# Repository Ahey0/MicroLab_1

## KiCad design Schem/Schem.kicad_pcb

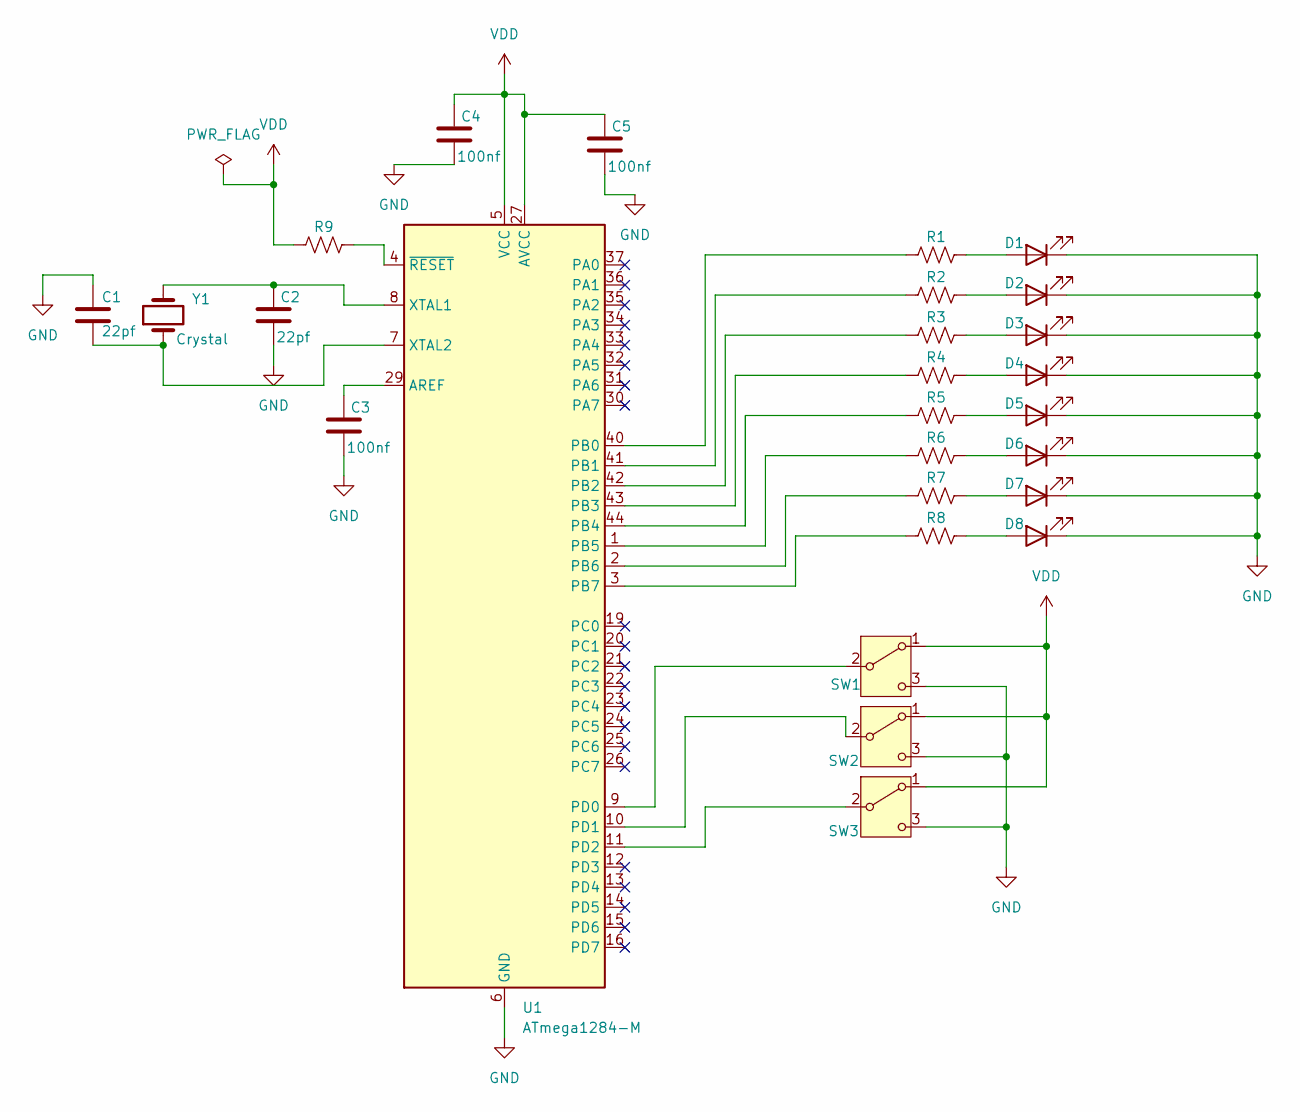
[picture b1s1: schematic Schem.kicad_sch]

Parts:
C1, C2: 22pf; C_0201_0603Metric
C3, C4, C5: 100nf; C_0201_0603Metric
D1, D2, D3, D5, D6, D7, D8: LED; LED_D3.0mm
D4: LED; LED_D3.0mm_FlatTop
R1, R2, R3, R4, R5, R6, R7, R8, R9: 10k; R_0402_1005Metric
SW1, SW2, SW3: SW_SPDT; SW_Slide_SPDT_Straight_CK_OS102011MS2Q
U1: ATmega1284-M; QFN-44-1EP_7x7mm_P0.5mm_EP5.2x5.2mm
Y1: Crystal; Crystal_SMD_EuroQuartz_EQ161-2Pin_3.2x1.5mm

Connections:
GND: C1.1, C2.2, C3.2, C4.2, C5.2, D1.1 (K), D2.1 (K), D3.1 (K), D4.1 (K), D5.1 (K), D6.1 (K), D7.1 (K), D8.1 (K), SW1.3 (C), SW2.3 (C), SW3.3 (C), U1.6 (GND), U1.18 (GND), U1.28 (GND), U1.39 (GND), U1.45 (GND)
unnamed: D1.2 (A), R1.2
unnamed: D2.2 (A), R2.2
unnamed: D3.2 (A), R3.2
unnamed: D4.2 (A), R4.2
unnamed: D5.2 (A), R5.2
unnamed: D6.2 (A), R6.2
unnamed: D7.2 (A), R7.2
unnamed: D8.2 (A), R8.2
unnamed: SW1.2 (B), U1.9 (PD0)
unnamed: SW2.2 (B), U1.10 (PD1)
unnamed: SW3.2 (B), U1.11 (PD2)
unnamed: C3.1, U1.29 (AREF)
unnamed: R1.1, U1.40 (PB0)
unnamed: R2.1, U1.41 (PB1)
unnamed: R3.1, U1.42 (PB2)
unnamed: R4.1, U1.43 (PB3)
unnamed: R5.1, U1.44 (PB4)
unnamed: R6.1, U1.1 (PB5)
unnamed: R7.1, U1.2 (PB6)
unnamed: R8.1, U1.3 (PB7)
unnamed: C2.1, U1.8 (XTAL1), Y1.2
unnamed: C1.2, U1.7 (XTAL2), Y1.1
unnamed: R9.2, U1.4 (~RESET)
VDD: C4.1, C5.1, R9.1, SW1.1 (A), SW2.1 (A), SW3.1 (A), U1.5 (VCC), U1.17 (VCC), U1.27 (AVCC), U1.38 (VCC)

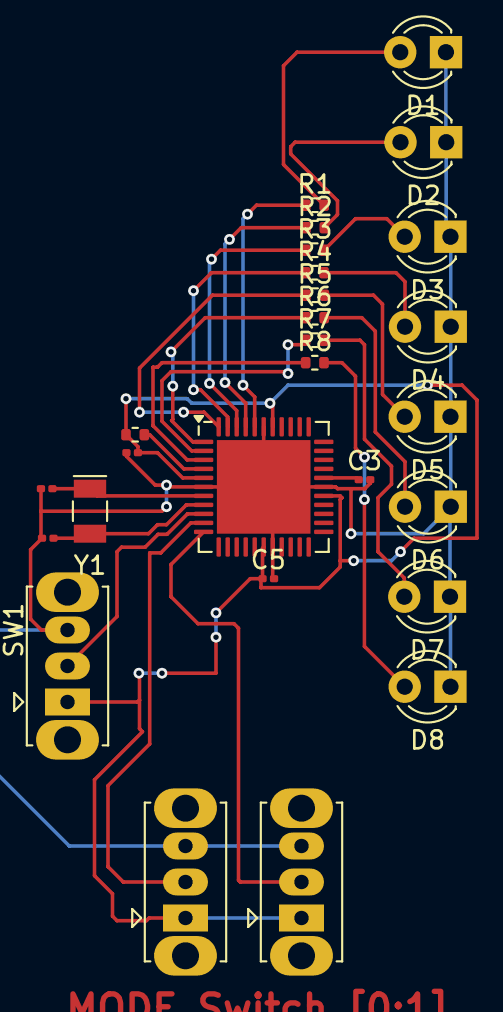
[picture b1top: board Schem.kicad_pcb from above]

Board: 2 copper layers, 27 parts (0 on the bottom side), 25 nets.

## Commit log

2025-03-11 Enteery
2025-03-11 Second
